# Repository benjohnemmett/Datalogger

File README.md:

# Datalogger
ATMega328-based custom data logger hardware &amp; firmware files. Currently, this project reads location data from a GPS module and writes it to a .csv file on an SD card. It is designed to work with a BN-220 GPS module.

Details of design, testing, and issues can be found here https://notes.benjemmett.com/archives/375

## Warning!
This project is in a rough draft state and currently includes significant hardware design issues.

- Incorrect exposed pad connection in 5v linear regulator
- GPS connector pad order does not match the cable provided with the BN-220 GPS module
- Missing FTDI DTR pin connection for programming with the Arduino bootloader
- Incorrect SD Card detect wiring causes light to always be on

## Log File Format
The log file consists of the BN-220 data written directly to a csv file. It can operate in two modes: 
1. Record only GGA messages
2. Record all messages

The Log File name format consists of a the date and a record number followed by the ".csv" extension. The format is as follows, DDMMYYXX.csv where:
- DD is the day of the month
- MM is month
- YY is the year
- XX is a record number incremented on each startup in the range [0-99]
For example, if the next record number is 42 and the current date is April 20, 2023 and the version number is 00 then the filename would be 20042342.csv

## Indicator Lights
The board includes 5 status LEDs numbered 0 to 4, where LED 0 is closest to the MCU. LED 0 indicates a critical error has occured.

Startup sequence is as follows:
1. Indicate DIP switch position.
  1. If DIP 1 is enabled, LED_3 blinks 3 times
  1. If DIP 2 is enabled, LED_4 blinks 3 times
1. Each LED blinks one time briefly in order from LED_0 to LED_4
1. Slow LED_1 toggling indicates an SD card failure. SD Card initialization is retried every 500ms until successful.
1. Three fast LED_1 blinks indicates successful SD card initialization.
1. LED_2 blinks indicate that GPS is being read and checked for synchronization before continuing.
1. LED_1 & LED_2 simultaneous blinks indicate that GPS data is being read until a valid date and time stamp is found.

During data collection:
- LED_3 is illuminated while reading GPS data
- LED_4 is illuminated while writing data to the SD card
- LED_0 is illuminated if there is an SD card write error

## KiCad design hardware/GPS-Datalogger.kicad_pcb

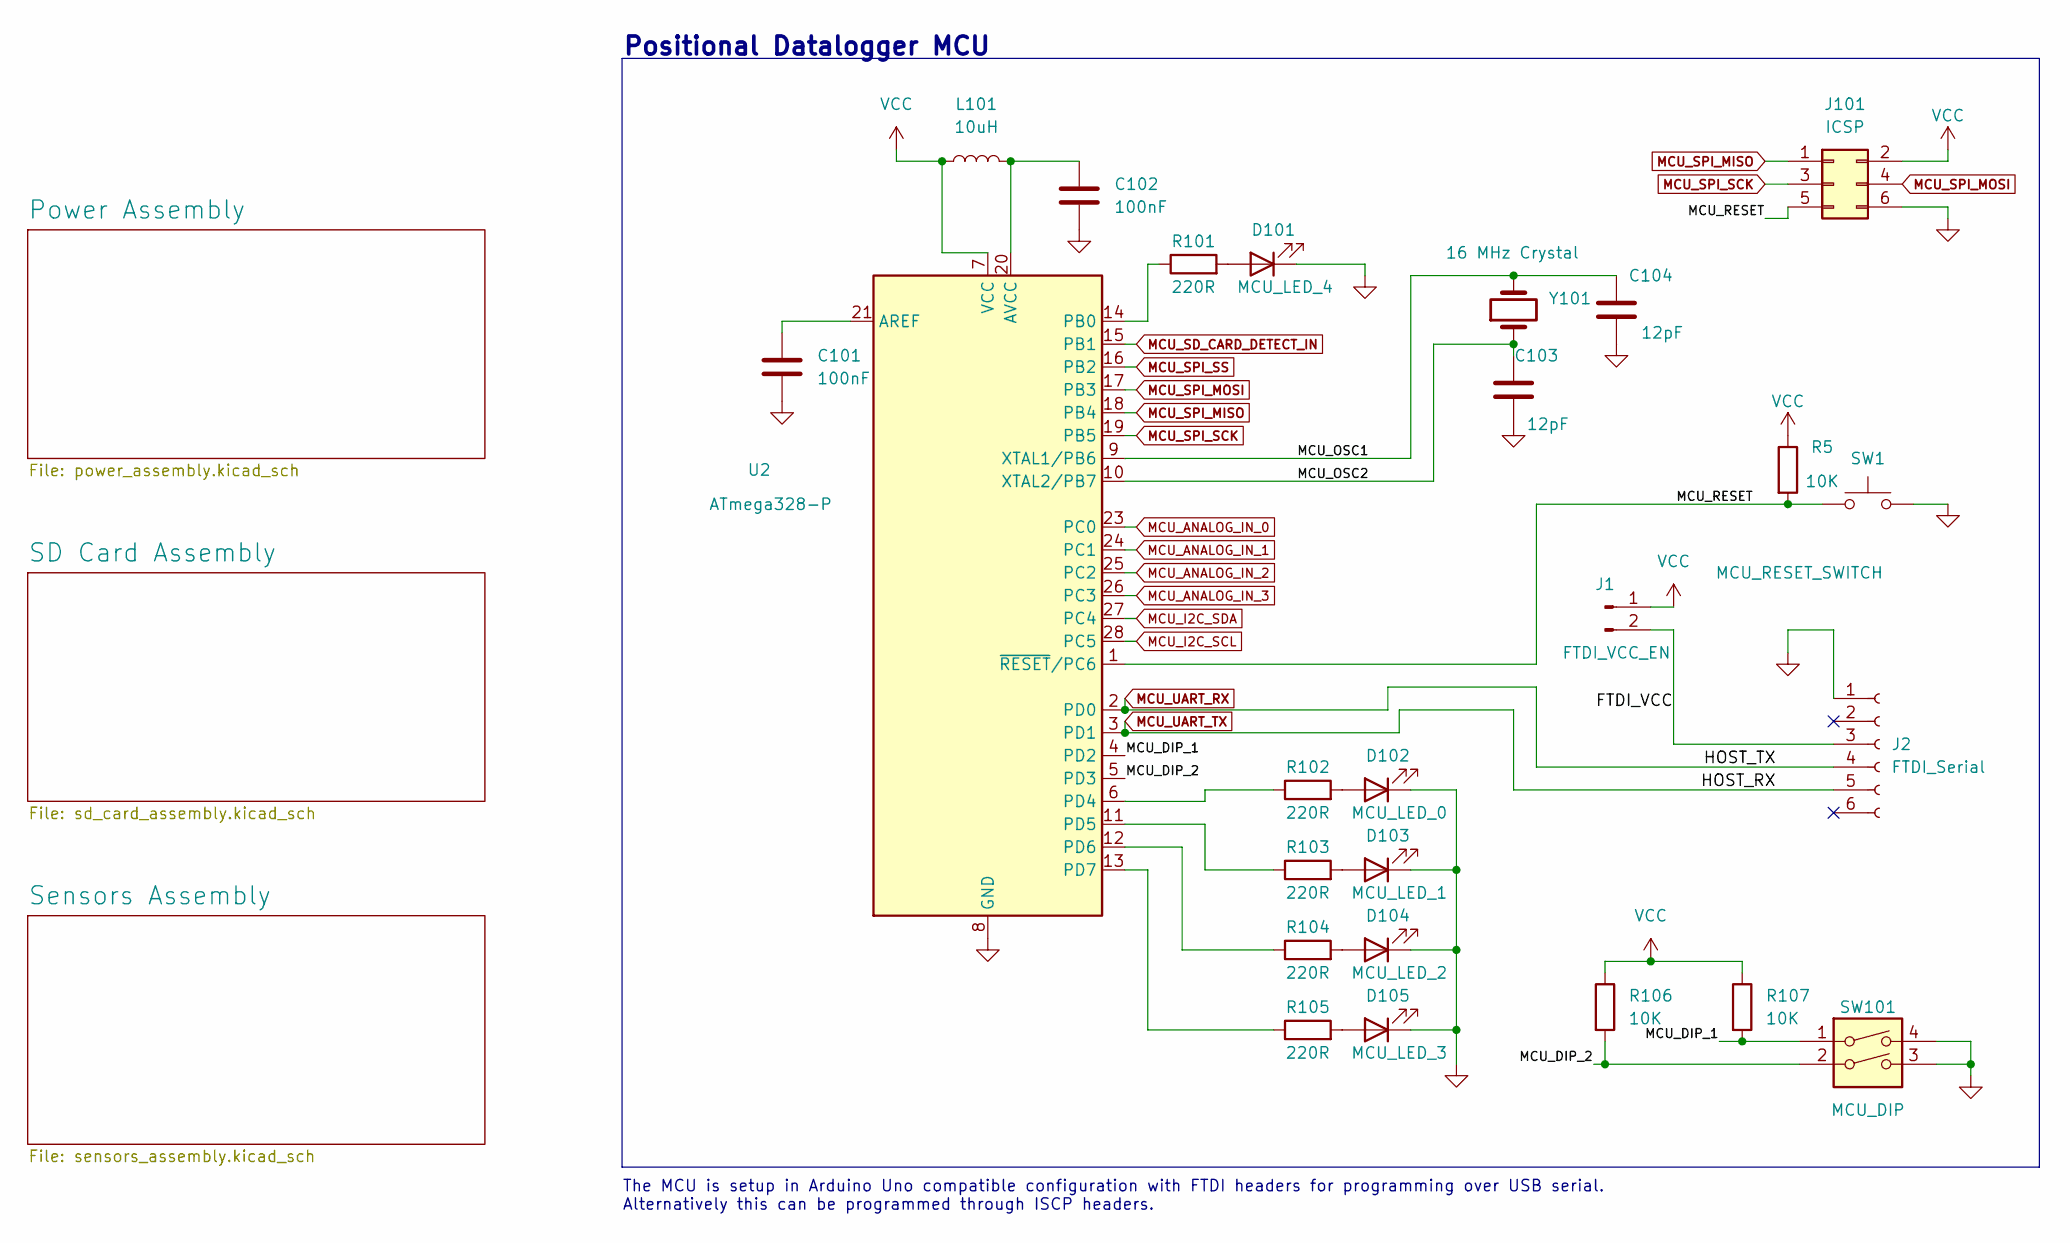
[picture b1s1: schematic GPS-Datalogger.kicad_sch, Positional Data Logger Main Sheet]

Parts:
C101, C102: 100nF; C_0805_2012Metric_Pad1.18x1.45mm_HandSolder
C103, C104: 12pF; C_0805_2012Metric_Pad1.18x1.45mm_HandSolder
D101: MCU_LED_4; LED_0805_2012Metric_Pad1.15x1.40mm_HandSolder
D102: MCU_LED_0; LED_0805_2012Metric_Pad1.15x1.40mm_HandSolder
D103: MCU_LED_1; LED_0805_2012Metric_Pad1.15x1.40mm_HandSolder
D104: MCU_LED_2; LED_0805_2012Metric_Pad1.15x1.40mm_HandSolder
D105: MCU_LED_3; LED_0805_2012Metric_Pad1.15x1.40mm_HandSolder
J1: FTDI_VCC_EN; PinHeader_1x02_P2.54mm_Vertical
J2: FTDI_Serial; PinSocket_1x06_P2.54mm_Vertical
J101: ICSP; PinHeader_2x03_P2.54mm_Vertical
L101: 10uH; L_Radial_D6.0mm_P4.00mm
R5, R106, R107: 10K; R_0805_2012Metric_Pad1.20x1.40mm_HandSolder
R101, R102, R103, R104, R105: 220R; R_0805_2012Metric_Pad1.20x1.40mm_HandSolder
SW1: MCU_RESET_SWITCH; SW_SPST_FSMSM
SW101: MCU_DIP; SW_DIP_SPSTx02_Slide_Copal_CHS-02B_W7.62mm_P1.27mm
U2: ATmega328-P; DIP-28_W7.62mm
Y101: 16 MHz Crystal; Crystal_HC18-U_Vertical

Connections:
/FTDI_VCC: J1.2, J2.3
/MCU_DIP_1: R107.2, SW101.1, U2.4 (PD2)
/MCU_DIP_2: R106.2, SW101.2, U2.5 (PD3)
/MCU_OSC1: C104.2, U2.9 (XTAL1/PB6), Y101.2
/MCU_OSC2: C103.2, U2.10 (XTAL2/PB7), Y101.1
/MCU_RESET: J101.5, R5.2, SW1.1 (A), U2.1 (~RESET/PC6)
GND: C101.2, C102.2, C103.1, C104.1, D101.1 (K), D102.1 (K), D103.1 (K), D104.1 (K), D105.1 (K), J2.1, J101.6, SW1.2 (B), SW101.3, SW101.4, U2.8 (GND), U2.22 (GND); also elsewhere on the board
MCU_ANALOG_IN_0: U2.23 (PC0); also elsewhere on the board
MCU_ANALOG_IN_1: U2.24 (PC1); also elsewhere on the board
MCU_ANALOG_IN_2: U2.25 (PC2); also elsewhere on the board
MCU_ANALOG_IN_3: U2.26 (PC3); also elsewhere on the board
MCU_I2C_SCL: U2.28 (PC5); also elsewhere on the board
MCU_I2C_SDA: U2.27 (PC4); also elsewhere on the board
MCU_SD_CARD_DETECT_IN: U2.15 (PB1); also elsewhere on the board
MCU_SPI_MISO: J101.1, U2.18 (PB4); also elsewhere on the board
MCU_SPI_MOSI: J101.4, U2.17 (PB3); also elsewhere on the board
MCU_SPI_SCK: J101.3, U2.19 (PB5); also elsewhere on the board
MCU_SPI_SS: U2.16 (PB2); also elsewhere on the board
MCU_UART_RX: J2.4, U2.2 (PD0); also elsewhere on the board
MCU_UART_TX: J2.5, U2.3 (PD1); also elsewhere on the board
unnamed: C101.1, U2.21 (AREF)
unnamed: C102.1, L101.2, U2.20 (AVCC)
unnamed: D101.2 (A), R101.2
unnamed: D102.2 (A), R102.2
unnamed: D103.2 (A), R103.2
unnamed: D104.2 (A), R104.2
unnamed: D105.2 (A), R105.2
unnamed: R101.1, U2.14 (PB0)
unnamed: R102.1, U2.6 (PD4)
unnamed: R103.1, U2.11 (PD5)
unnamed: R104.1, U2.12 (PD6)
unnamed: R105.1, U2.13 (PD7)
VCC: J1.1, J101.2, L101.1, R5.1, R106.1, R107.1, U2.7 (VCC); also elsewhere on the board

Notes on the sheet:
Positional Datalogger MCU
The MCU is setup in Arduino Uno compatible configuration with FTDI headers for programming over USB serial. Alternatively this can be programmed through ISCP headers.

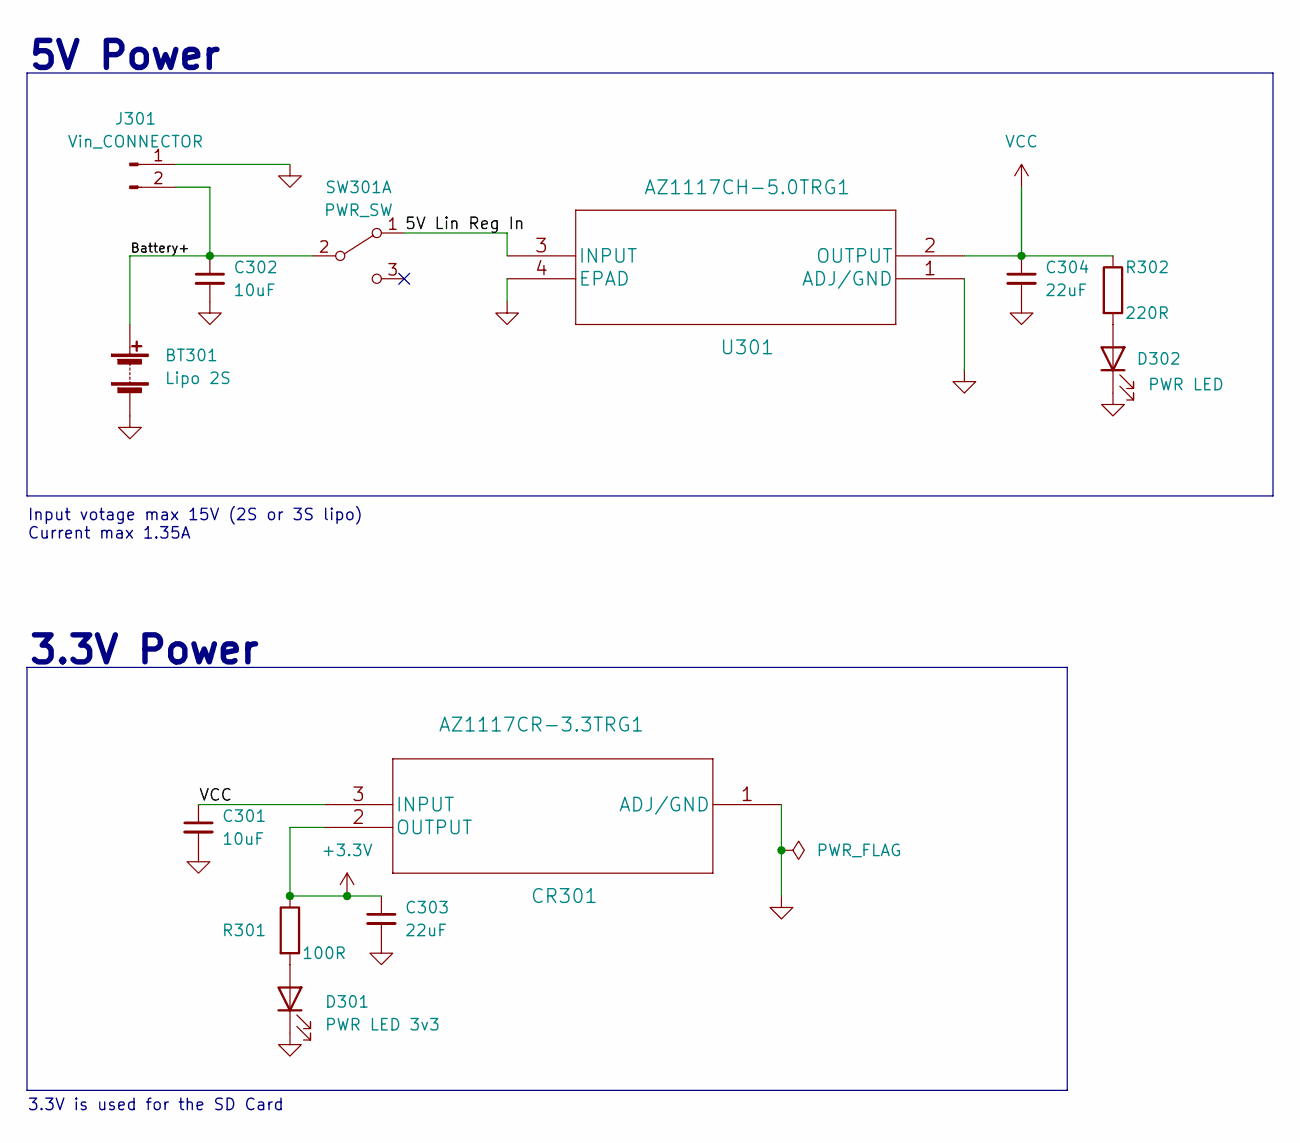
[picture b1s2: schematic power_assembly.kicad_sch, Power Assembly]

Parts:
BT301: Lipo 2S; AMASS_XT30U-M_1x02_P5.0mm_Vertical
C301, C302: 10uF; CP_Radial_D4.0mm_P1.50mm
C303, C304: 22uF; CP_Radial_D4.0mm_P1.50mm
CR301: AZ1117CR-3.3TRG1
D301: PWR LED 3v3; LED_0805_2012Metric_Pad1.15x1.40mm_HandSolder
D302: PWR LED; LED_0805_2012Metric_Pad1.15x1.40mm_HandSolder
J301: Vin_CONNECTOR; PinHeader_1x02_P2.54mm_Vertical
R301: 100R; R_0805_2012Metric_Pad1.20x1.40mm_HandSolder
R302: 220R; R_0805_2012Metric_Pad1.20x1.40mm_HandSolder
SW301: PWR_SW; SW_DPDT_MSS22D18_6pin_bje
U301: AZ1117CH-5.0TRG1

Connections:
+3V3: C303.1, CR301.2 (OUTPUT), R301.1; also elsewhere on the board
/Power Assembly/5V Lin Reg In: SW301.1 (A), U301.3 (INPUT)
/Power Assembly/Battery+: BT301.2 (+), C302.1, J301.2, SW301.2 (B)
GND: BT301.1 (-), C301.2, C302.2, C303.2, C304.2, CR301.1 (ADJ/GND), D301.1 (K), D302.1 (K), J301.1, U301.1 (ADJ/GND), U301.4 (EPAD); also elsewhere on the board
unnamed: D301.2 (A), R301.2
unnamed: D302.2 (A), R302.2
VCC: C301.1, C304.1, CR301.3 (INPUT), R302.1, U301.2 (OUTPUT); also elsewhere on the board

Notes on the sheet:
3.3V is used for the SD Card
3.3V Power
Input votage max 15V (2S or 3S lipo) Current max 1.35A
5V Power

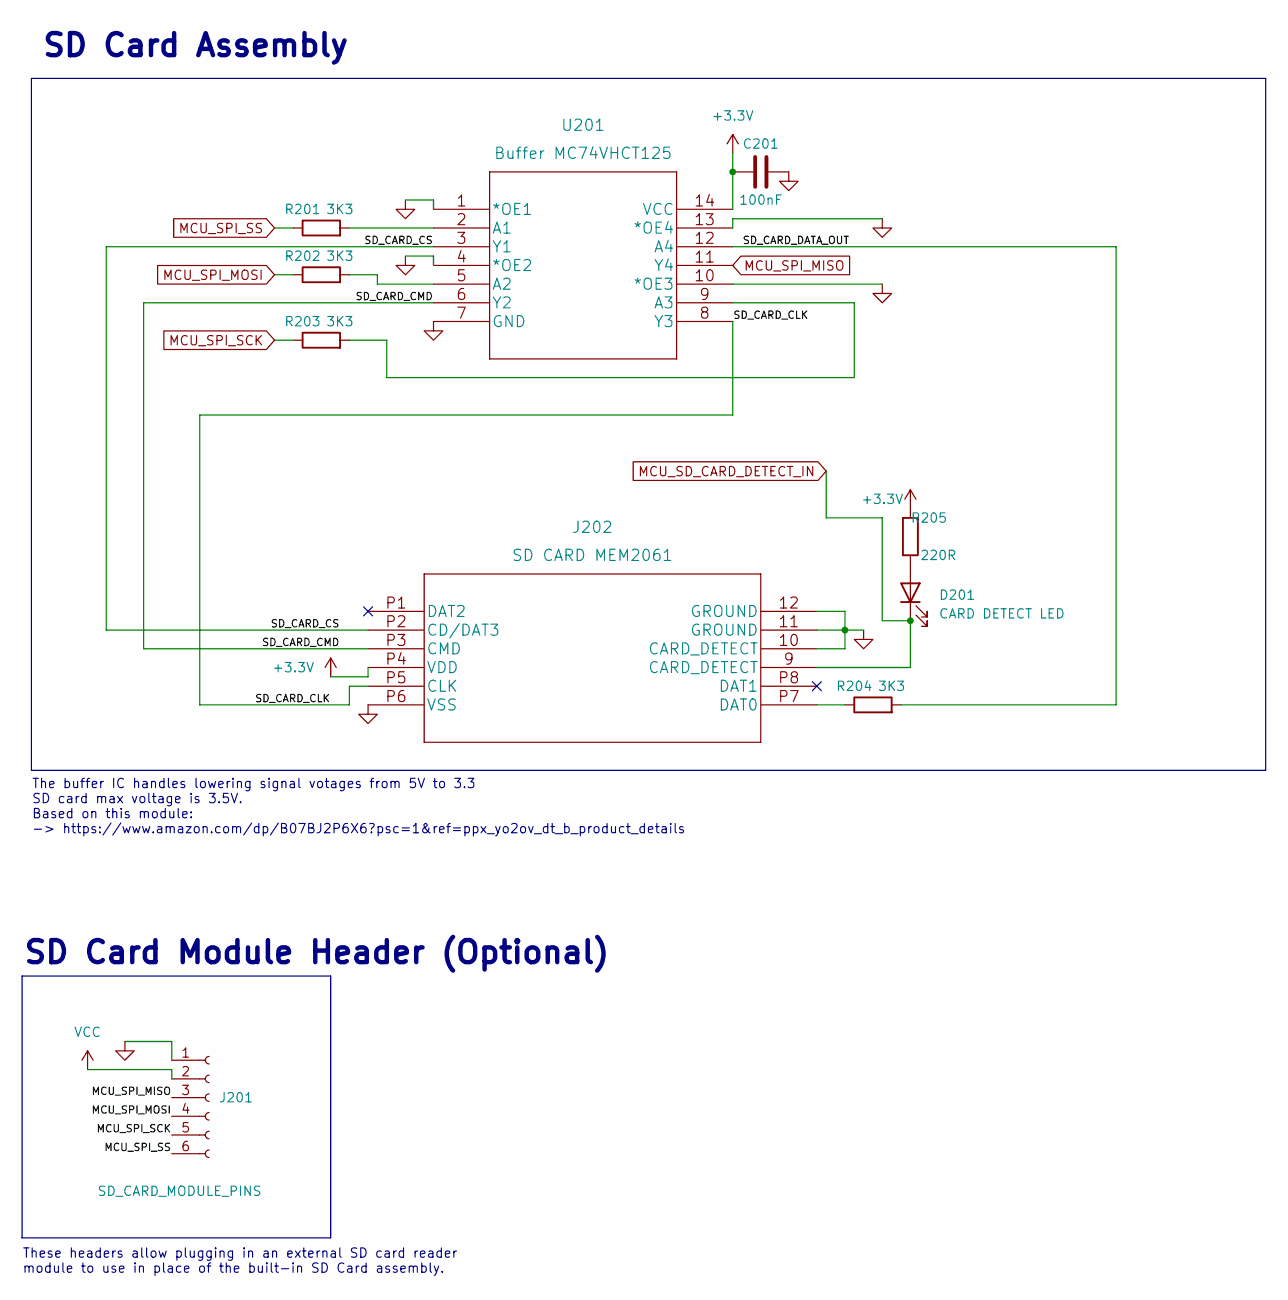
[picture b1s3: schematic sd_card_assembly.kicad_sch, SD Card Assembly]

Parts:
C201: 100nF; C_0805_2012Metric_Pad1.18x1.45mm_HandSolder
D201: CARD DETECT LED; LED_0805_2012Metric_Pad1.15x1.40mm_HandSolder
J201: SD_CARD_MODULE_PINS; PinSocket_1x06_P2.54mm_Vertical
J202: SD CARD MEM2061; MEM2061
R201, R202, R203, R204: 3K3; R_0805_2012Metric_Pad1.20x1.40mm_HandSolder
R205: 220R; R_0805_2012Metric_Pad1.20x1.40mm_HandSolder
U201: Buffer MC74VHCT125; MC74VHCT125ADR2G

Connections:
+3V3: C201.1, J202.P4 (VDD), R205.1, U201.14 (VCC); also elsewhere on the board
/SD Card Assembly/SD_CARD_CLK: J202.P5 (CLK), U201.8 (Y3)
/SD Card Assembly/SD_CARD_CMD: J202.P3 (CMD), U201.6 (Y2)
/SD Card Assembly/SD_CARD_CS: J202.P2 (CD/DAT3), U201.3 (Y1)
/SD Card Assembly/SD_CARD_DATA_OUT: R204.2, U201.12 (A4)
GND: C201.2, J201.1, J202.10 (CARD_DETECT), J202.11 (GROUND), J202.12 (GROUND), J202.P6 (VSS), U201.1 (*OE1), U201.4 (*OE2), U201.7 (GND), U201.10 (*OE3), U201.13 (*OE4); also elsewhere on the board
MCU_SD_CARD_DETECT_IN: D201.1 (K), J202.9 (CARD_DETECT); also elsewhere on the board
MCU_SPI_MISO: J201.3, U201.11 (Y4); also elsewhere on the board
MCU_SPI_MOSI: J201.4, R202.1; also elsewhere on the board
MCU_SPI_SCK: J201.5, R203.1; also elsewhere on the board
MCU_SPI_SS: J201.6, R201.1; also elsewhere on the board
unnamed: D201.2 (A), R205.2
unnamed: J202.P7 (DAT0), R204.1
unnamed: R201.2, U201.2 (A1)
unnamed: R202.2, U201.5 (A2)
unnamed: R203.2, U201.9 (A3)
VCC: J201.2; also elsewhere on the board

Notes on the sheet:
The buffer IC handles lowering signal votages from 5V to 3.3 SD card max voltage is 3.5V. Based on this module: -> https://www.amazon.com/dp/B07BJ2P6X6?psc=1&ref=ppx_yo2ov_dt_b_product_details
SD Card Module Header (Optional)
SD Card Assembly
These headers allow plugging in an external SD card reader module to use in place of the built-in SD Card assembly.

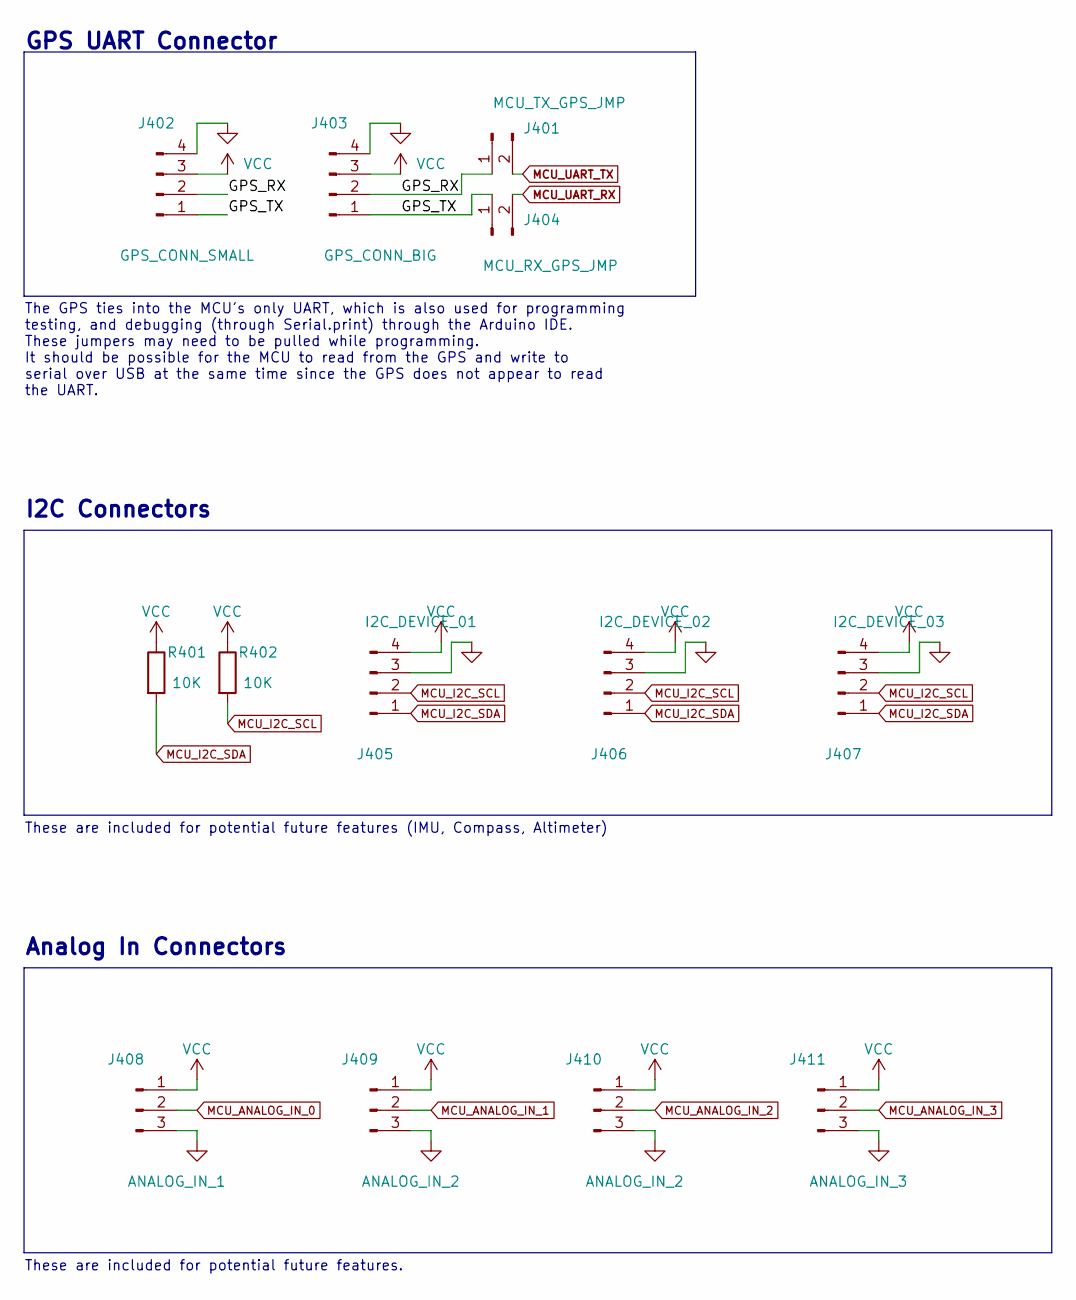
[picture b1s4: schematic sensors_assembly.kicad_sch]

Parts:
J401: MCU_TX_GPS_JMP; PinSocket_1x02_P2.54mm_Vertical
J402: GPS_CONN_SMALL; CONN_BM04B-SRSS-TB(LF)(SN)
J403: GPS_CONN_BIG; PinSocket_1x04_P2.54mm_Vertical
J404: MCU_RX_GPS_JMP; PinSocket_1x02_P2.54mm_Vertical
J405: I2C_DEVICE_01; JST_PH_B4B-PH-K_1x04_P2.00mm_Vertical
J406: I2C_DEVICE_02; JST_PH_B4B-PH-K_1x04_P2.00mm_Vertical
J407: I2C_DEVICE_03; JST_PH_B4B-PH-K_1x04_P2.00mm_Vertical
J408: ANALOG_IN_1; JST_PH_B3B-PH-K_1x03_P2.00mm_Vertical
J409, J410: ANALOG_IN_2; JST_PH_B3B-PH-K_1x03_P2.00mm_Vertical
J411: ANALOG_IN_3; JST_PH_B3B-PH-K_1x03_P2.00mm_Vertical
R401, R402: 10K; R_0805_2012Metric_Pad1.20x1.40mm_HandSolder

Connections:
/Sensors Assembly/GPS_RX: J401.1, J402.2, J403.2
/Sensors Assembly/GPS_TX: J402.1, J403.1, J404.1
GND: J402.4, J403.4, J405.3, J406.3, J407.3, J408.3, J409.3, J410.3, J411.3; also elsewhere on the board
MCU_ANALOG_IN_0: J408.2; also elsewhere on the board
MCU_ANALOG_IN_1: J409.2; also elsewhere on the board
MCU_ANALOG_IN_2: J410.2; also elsewhere on the board
MCU_ANALOG_IN_3: J411.2; also elsewhere on the board
MCU_I2C_SCL: J405.2, J406.2, J407.2, R402.2; also elsewhere on the board
MCU_I2C_SDA: J405.1, J406.1, J407.1, R401.2; also elsewhere on the board
MCU_UART_RX: J404.2; also elsewhere on the board
MCU_UART_TX: J401.2; also elsewhere on the board
VCC: J402.3, J403.3, J405.4, J406.4, J407.4, J408.1, J409.1, J410.1, J411.1, R401.1, R402.1; also elsewhere on the board

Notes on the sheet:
The GPS ties into the MCU's only UART, which is also used for programming testing, and debugging (through Serial.print) through the Arduino IDE. These jumpers may need to be pulled while programming. It should be possible for the MCU to read from the GPS and write to serial over USB at the same tim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
These are included for potential future features (IMU, Compass, Altimeter)
GPS UART Connector
These are included for potential future features.
Analog In Connectors
I2C Connectors

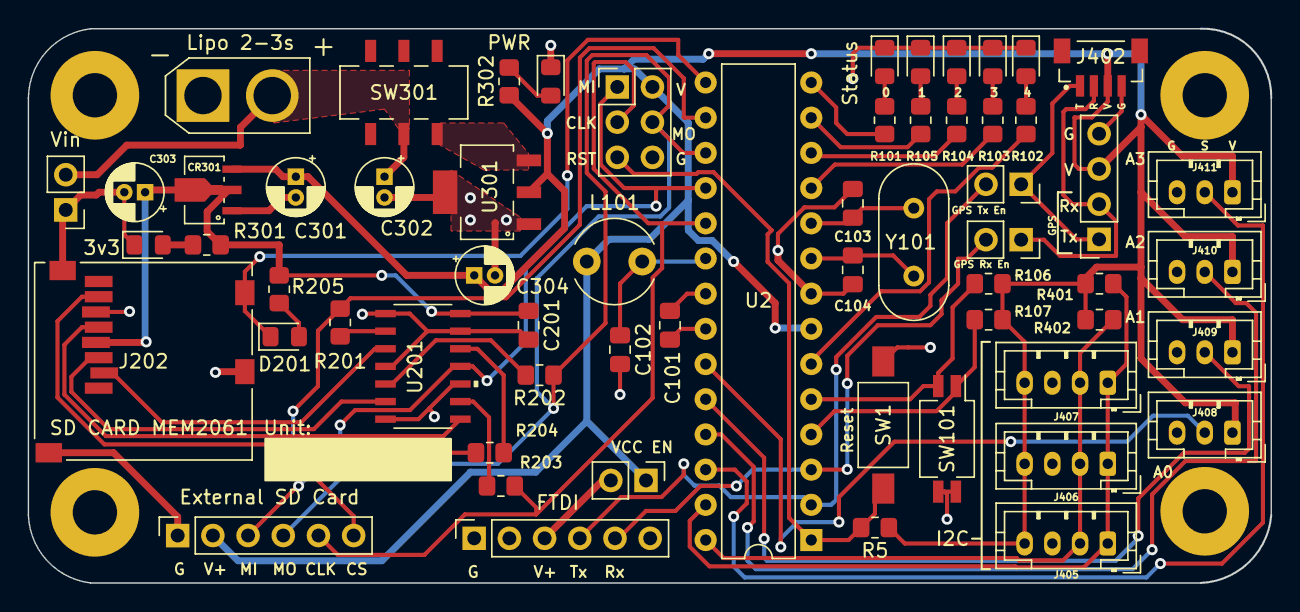
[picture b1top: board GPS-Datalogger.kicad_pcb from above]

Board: 2 copper layers, 89.7 x 40.0 mm, 65 parts (0 on the bottom side), 49 nets.

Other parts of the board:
TH0, TH1, TH3: MountingHole_3.2mm_M3_Pad
TH2: (no value)

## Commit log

2022-07-27 Initial commit with hardware files.
2022-07-29 Initial data logger firmware. Tested, recording GPS data to SD card.
2022-08-04 Moved GPS utils to separate header file.
2022-08-04 Added python tool for reformatting collected gps data.
2022-08-12 over-engineer
2023-04-21 Dynamic log file names based on date & record number.
2023-04-22 Updated firmware to only open the log file when data is ready to write.
2023-04-27 WIP: Partially tested. On hold due to hardware issues. Asserting DIP enabls all serial data to be written to the SD card.
2023-05-06 Minor firmware cleanup. Verified with hardware.
2024-04-03 DIP switch 1 activate WRITE_ALL mode.

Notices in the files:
parts and their libraries:
Copyright 2021 Accelerated Designs. All rights reserved.
